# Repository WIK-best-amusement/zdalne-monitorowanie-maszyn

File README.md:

Projekt służy do zdalnego monitorowania pracy różnych urządzeń rozrywkowych, takich jak airhockey'e, maszyny do gry w koszykówkę czy też inne automaty do gier. Informację o ilości rozegranych gier, parametrach pracy urządzenia, oraz innych informacjach są przesyłane do serwera, gdzie są przechowywane i wyświetlane w formie wykresów i tabel.
Dodatkowo serwer pozwala na zdalne sterowanie urządzeniami, np. zmianę ilości punktów potrzebnych do wygrania gry, czy też zmianę ilości kredytów potrzebnych do rozpoczęcia gry. Dodatkowo na podstawie przesyłanych przez urządzenie parametrów pracy, serwer jest w stanie wykryć awarie urządzenia i wyświetlać ostrzeżenia o nich właścicielowi urządzenia.
Projekt zawiera wszystkie komponenty potrzebne do uruchomienia systemu, w tym:
- Projekt płytki PCB z modułem WiFi, pozwalającej na podłączenie urządzenia do sieci WiFi i przesyłanie danych do serwera
- Projekt oprogramowania dla modułu WiFi, pozwalającego na podłączenie się do sieci WiFi i przesyłanie danych do serwera
- Projekt bazy danych która należy uruchomić na serwerze i do której łączą się urządzenia, pozwala ona także na zarządzanie urządzeniami oraz sprawdzanie ich stanu oraz na bierząco monitoruje ich parametry pracy i wykrywa awarie.

Udostepniony projekt pozwala na dalsze rozwiniecie systemu, np. o dodatkowe urządzenia, lub też o dodatkowe funkcjonalności czy integracje z innymi systemami, na przykład wewnętrznymi systemami zarządzania istniejącymi w firmach klientów.

Projekt został stworzony w ramach dofinansowania ze środków Unii Europejskiej

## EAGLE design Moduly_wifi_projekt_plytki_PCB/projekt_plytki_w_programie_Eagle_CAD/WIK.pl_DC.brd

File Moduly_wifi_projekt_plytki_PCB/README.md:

Wszystkie pliki projektowe dotyczące płytki PCB z modułem WiFi, w katalogach znajdują się opowiednio:

BOM - lista elementów elektrycznych znajdujących się na płytce

gerbery - pliki projektu w formacie 'gerber' pozwalające na wyprodukowanie płytki PCB modułu WiFi u dowolnego producenta płytek PCB

pliki montażowe - pliki opisujące dokładne pozycje elementów elektrycznych na płytce (wymienionych w 'BOM'), pozwalają na zautomatyzowana produkcję płytek modułów

projekt_plytki_w_programie_Eagle_CAD - edytowalny projekt płytki PCB utworzony w programie Eagle CAD, pozwala na modyfikację projektu

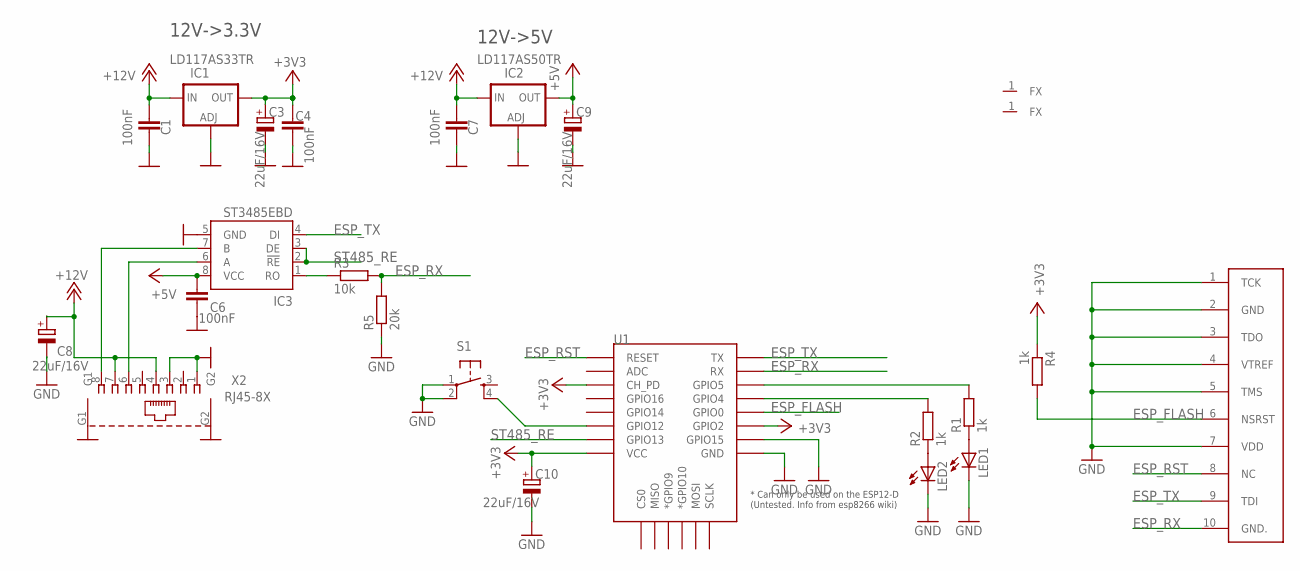
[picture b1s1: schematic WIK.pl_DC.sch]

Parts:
C1, C4, C6, C7: 100nF; C0805
C3, C8, C9, C10: 22uF/16V; SMC_B
IC1: LD117AS33TR; SOT223
IC2: LD117AS50TR; SOT223
IC3: ST3485EBD; SOIC8
LED1, LED2: LED1206; LED-1206
R1, R2, R4: 1k; R0805
R3: 10k; R0805
R5: 20k; R0805
S1: TAC_SWITCHPTH; TACTILE-PTH
U1: ESP12ESMD; ESP12E-SMD
U$1, U$2: FIDUCIAL
U$3: TC2050-IDC-NL
X2: RJ45-8X; RJ45-NO-SHIELD

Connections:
+3V3: C3.+, C4.1, C10.+, IC1.4 (OUT), R4.1, U1.CH_PD, U1.GPIO2, U1.VCC
+5V: C6.2, C9.+, IC2.4 (OUT), IC3.8 (VCC)
+12V: C1.1, C7.1, C8.+, IC1.3 (IN), IC2.3 (IN), X2.4, X2.7
ESP_FLASH: R4.2, U1.GPIO0, U$3.6 (NSRST)
ESP_RST: U1.RESET, U$3.8 (NC)
ESP_RX: R3.2, R5.2, U1.RXD0 (RX), U$3.10 (GND.)
ESP_TX: IC3.4 (DI), U1.TXD0 (TX), U$3.9 (TDI)
GND: C1.2, C3.-, C4.2, C6.1, C7.2, C8.-, C9.-, C10.-, IC1.1 (ADJ), IC2.1 (ADJ), IC3.5 (GND), LED1.C, LED2.C, R5.1, S1.1, S1.2, U1.GND, U1.GPIO15, U$3.1 (TCK), U$3.2 (GND), U$3.3 (TDO), U$3.4 (VTREF), U$3.5 (TMS), U$3.7 (VDD), X2.1, X2.3, X2.G1, X2.G2
unnamed: IC3.7 (B), X2.8
unnamed: R1.2, U1.GPIO5
unnamed: IC3.6 (A), X2.6
unnamed: LED1.A, R1.1
unnamed: LED2.A, R2.1
unnamed: R2.2, U1.GPIO4
unnamed: S1.4, U1.GPIO12
unnamed: IC3.1 (RO), R3.1
ST485_RE: IC3.2 (!RE), IC3.3 (DE), U1.GPIO13

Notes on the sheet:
12V->3.3V
12V->5V

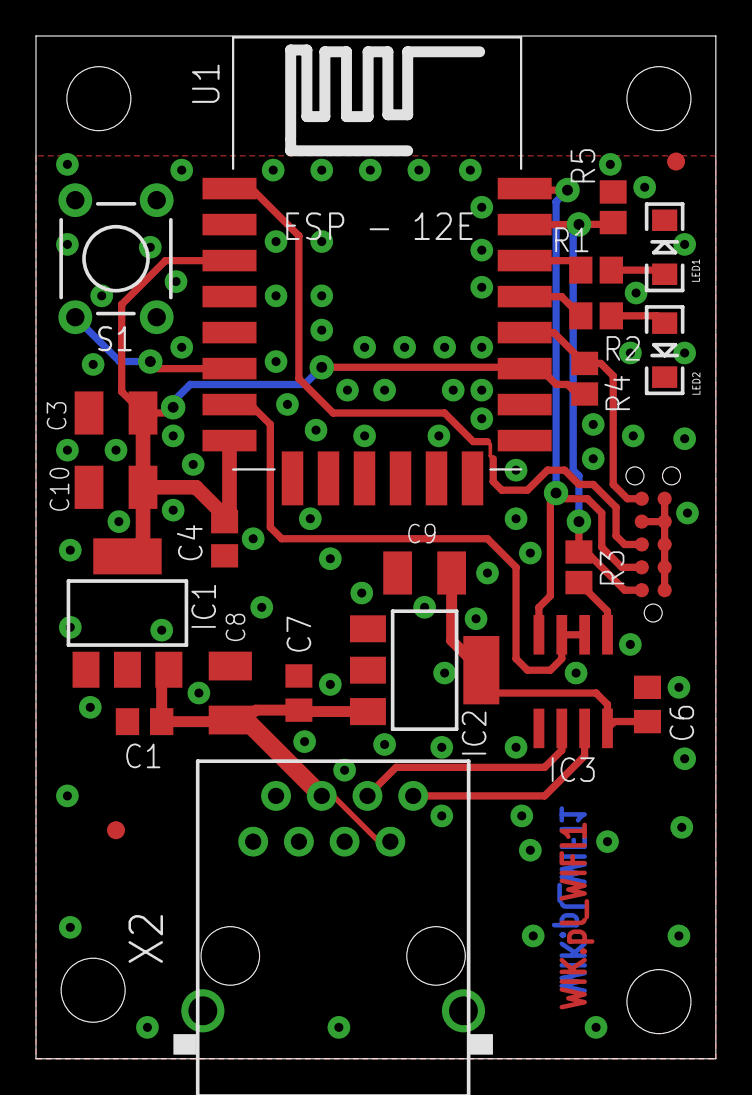
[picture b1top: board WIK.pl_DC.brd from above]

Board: 2 copper layers, 37.8 x 56.8 mm, 24 parts (0 on the bottom side), 17 nets.

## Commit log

2023-09-08 dodane logotypy

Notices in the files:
parts and their libraries:
SparkFun: Licensing: CC v3.0 Share-Alike You are welcome to use this library for commercial purposes.
